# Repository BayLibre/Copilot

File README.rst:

Copilot
=======

.. image:: doc/source/pictures/copilot_lite_top.jpg

Description
-----------

The user documentation is available in the ``doc`` folder.
The generated HTML pages can be viewed `here <https://baylibre.github.io/Copilot/>`_.

The board hardware files are in the ``Copilot_Lite/Hardware`` folder.

The FTDI chip is configured and serialized by the ``Serialization`` software located in the  ``Copilot_Lite/Software`` folder.
The boards serialization and test procedure is described in the ``Copilot_Lite/Factory_Testing.md`` file.

Extension boards
----------------

The Copilot Lite board features some extension boards to be connected on top, like an Arduino Shield or a Raspberry Pi Hat.

More than one extension board can be stacked on top of the Copilot Lite master board, according to the needs.

* `3x USB 2.0 channels <https://github.com/BayLibre/Copilot-extension-triple-usb-2.0>`_, the Copilot Lite GPIOs can drive the channels power.
* `3x signal relays <https://github.com/BayLibre/Copilot_Extension_Triple_Relays>`_, the Copilot Lite GPIOs can close or open each relay.

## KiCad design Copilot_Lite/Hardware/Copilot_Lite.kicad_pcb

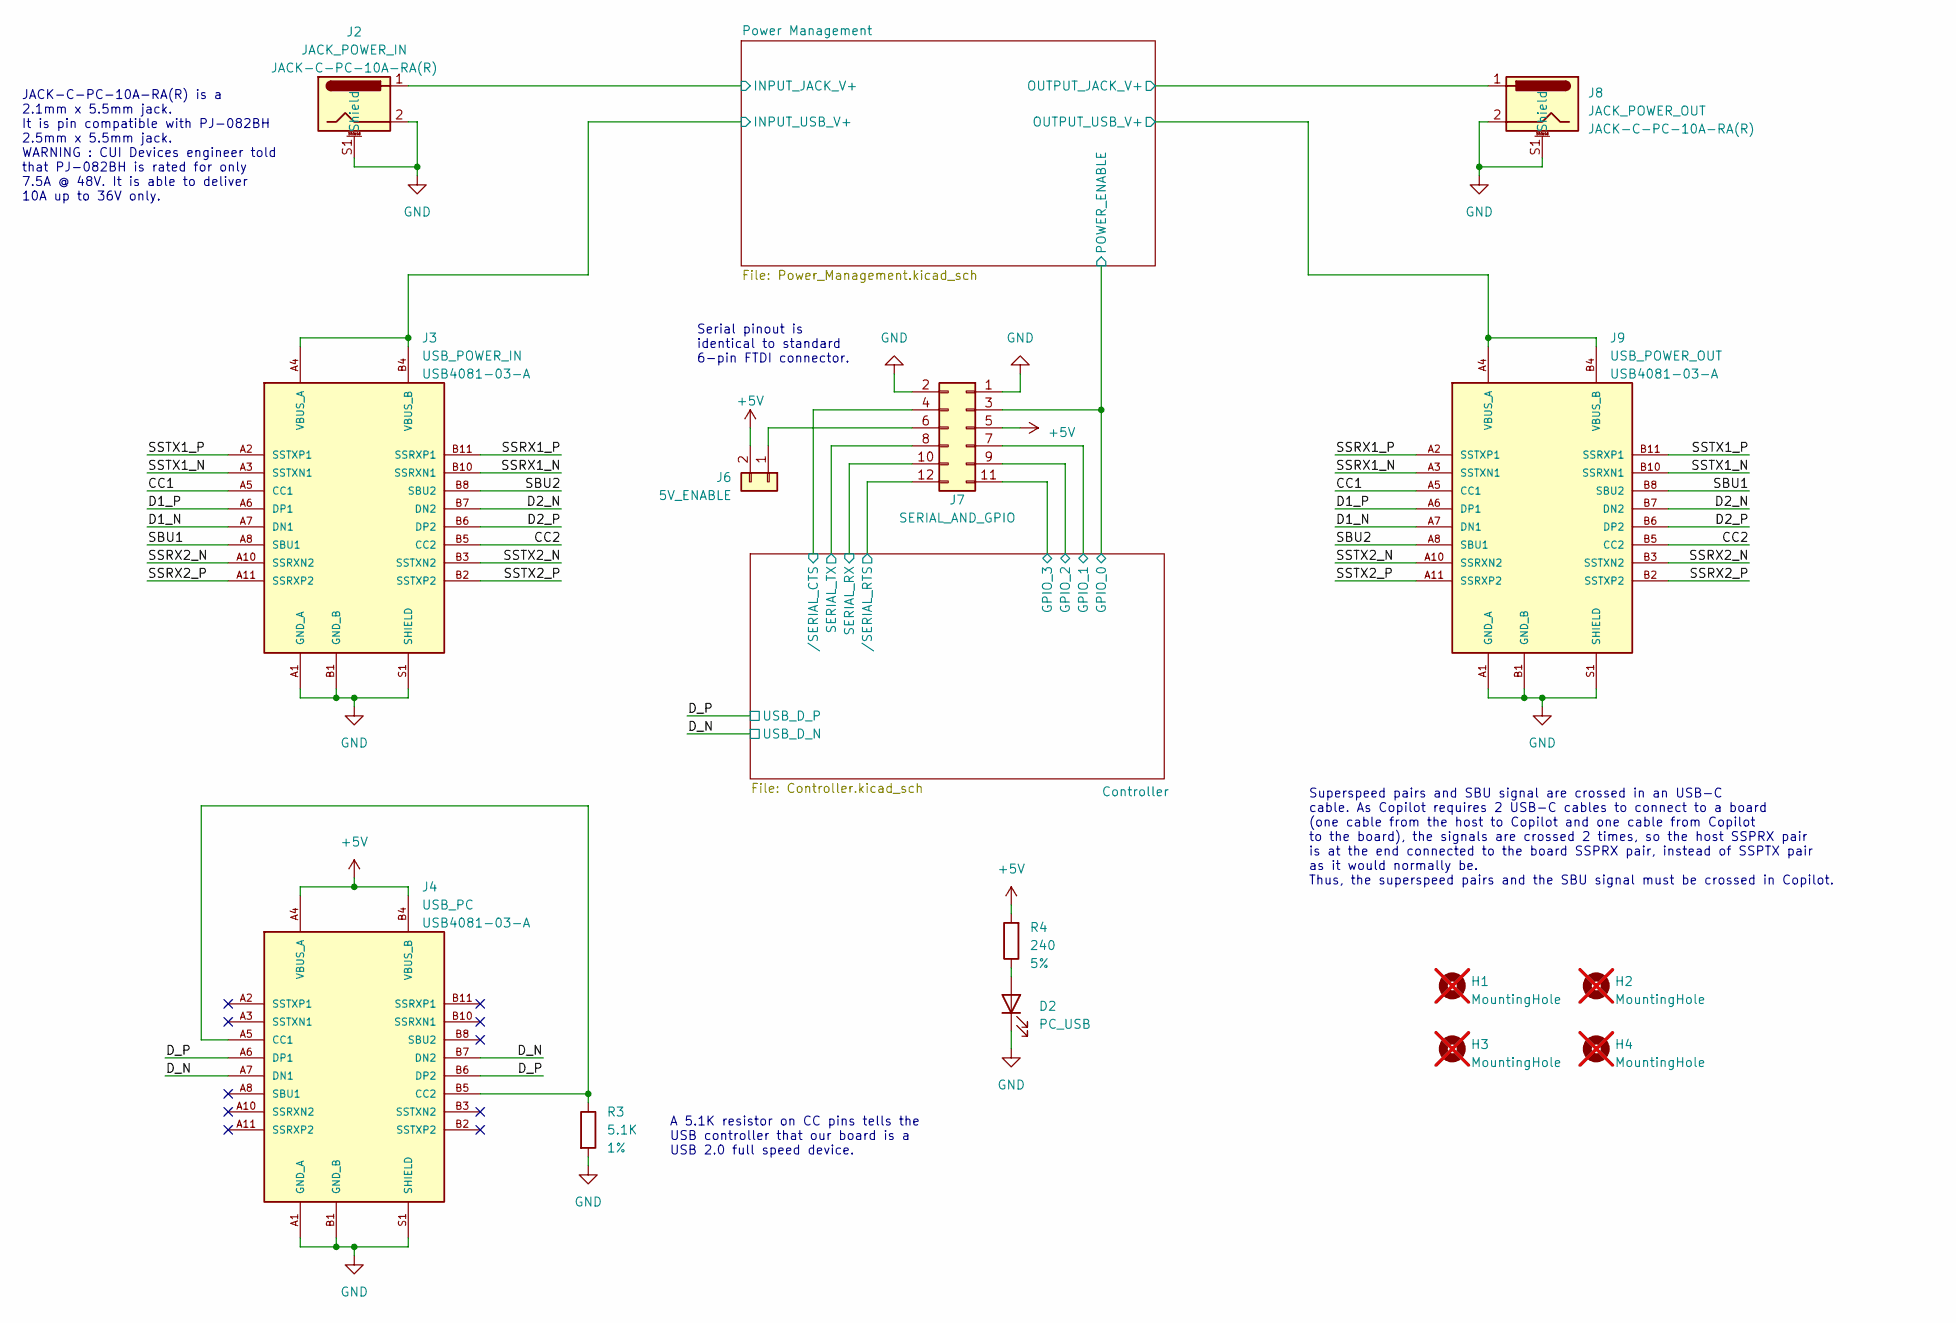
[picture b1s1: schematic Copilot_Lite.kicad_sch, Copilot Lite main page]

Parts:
D2: PC_USB; LED_0805_2012Metric; PartNumber 150080SS75000
H1, H2, H3, H4: MountingHole; MountingHole_2.7mm; not fitted
J2: JACK_POWER_IN; JACK-C-PC-10A-RA(R); PartNumber JACK-C-PC-10A-RA(R)
J3: USB_POWER_IN; USB4081-03-A; PartNumber USB4081-03-A
J4: USB_PC; USB4081-03-A; PartNumber USB4081-03-A
J6: 5V_ENABLE; PinHeader_1x02_P2.54mm_Horizontal
J7: SERIAL_AND_GPIO; PinHeader_2x06_P2.54mm_Horizontal
J8: JACK_POWER_OUT; JACK-C-PC-10A-RA(R); PartNumber JACK-C-PC-10A-RA(R)
J9: USB_POWER_OUT; USB4081-03-A; PartNumber USB4081-03-A
R3: 5.1K; R_0603_1608Metric; PartNumber RC0603FR-075K1L
R4: 240; R_1206_3216Metric; PartNumber RC1206JR-07240RL

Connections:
+5V: J4.A4 (VBUS_A), J4.A9 (VBUS_A), J4.B4 (VBUS_B), J4.B9 (VBUS_B), J6.2, J7.5, R4.2; also elsewhere on the board
/CC1: J3.A5 (CC1), J9.A5 (CC1)
/CC2: J3.B5 (CC2), J9.B5 (CC2)
/Controller/GPIO_0: J7.3; also elsewhere on the board
/Controller/GPIO_1: J7.7; also elsewhere on the board
/Controller/GPIO_2: J7.9; also elsewhere on the board
/Controller/GPIO_3: J7.11; also elsewhere on the board
/Controller/SERIAL_RX: J7.10; also elsewhere on the board
/Controller/SERIAL_TX: J7.8; also elsewhere on the board
/Controller//SERIAL_CTS: J7.4; also elsewhere on the board
/Controller//SERIAL_RTS: J7.12; also elsewhere on the board
/D1_N: J3.A7 (DN1), J9.A7 (DN1)
/D1_P: J3.A6 (DP1), J9.A6 (DP1)
/D2_N: J3.B7 (DN2), J9.B7 (DN2)
/D2_P: J3.B6 (DP2), J9.B6 (DP2)
/D_N: J4.A7 (DN1), J4.B7 (DN2); also elsewhere on the board
/D_P: J4.A6 (DP1), J4.B6 (DP2); also elsewhere on the board
/Power Management/INPUT_JACK_V+: J2.1; also elsewhere on the board
/Power Management/INPUT_USB_V+: J3.A4 (VBUS_A), J3.A9 (VBUS_A), J3.B4 (VBUS_B), J3.B9 (VBUS_B); also elsewhere on the board
/Power Management/OUTPUT_JACK_V+: J8.1; also elsewhere on the board
/Power Management/OUTPUT_USB_V+: J9.A4 (VBUS_A), J9.A9 (VBUS_A), J9.B4 (VBUS_B), J9.B9 (VBUS_B); also elsewhere on the board
/SBU1: J3.A8 (SBU1), J9.B8 (SBU2)
/SBU2: J3.B8 (SBU2), J9.A8 (SBU1)
/SSRX1_N: J3.B10 (SSRXN1), J9.A3 (SSTXN1)
/SSRX1_P: J3.B11 (SSRXP1), J9.A2 (SSTXP1)
/SSRX2_N: J3.A10 (SSRXN2), J9.B3 (SSTXN2)
/SSRX2_P: J3.A11 (SSRXP2), J9.B2 (SSTXP2)
/SSTX1_N: J3.A3 (SSTXN1), J9.B10 (SSRXN1)
/SSTX1_P: J3.A2 (SSTXP1), J9.B11 (SSRXP1)
/SSTX2_N: J3.B3 (SSTXN2), J9.A10 (SSRXN2)
/SSTX2_P: J3.B2 (SSTXP2), J9.A11 (SSRXP2)
GND: D2.1 (K), J2.2, J2.S1 (Shield), J2.S2 (Shield), J2.S3 (Shield), J2.S4 (Shield), J3.A1 (GND_A), J3.A12 (GND_A), J3.B1 (GND_B), J3.B12 (GND_B), J3.S1 (SHIELD), J3.S2 (SHIELD), J3.S3 (SHIELD), J3.S4 (SHIELD), J3.S5 (SHIELD), J3.S6 (SHIELD), J4.A1 (GND_A), J4.A12 (GND_A), J4.B1 (GND_B), J4.B12 (GND_B), J4.S1 (SHIELD), J4.S2 (SHIELD), J4.S3 (SHIELD), J4.S4 (SHIELD), J4.S5 (SHIELD), J4.S6 (SHIELD), J7.1, J7.2, J8.2, J8.S1 (Shield), J8.S2 (Shield), J8.S3 (Shield), J8.S4 (Shield), J9.A1 (GND_A), J9.A12 (GND_A), J9.B1 (GND_B), J9.B12 (GND_B), J9.S1 (SHIELD), J9.S2 (SHIELD), J9.S3 (SHIELD), J9.S4 (SHIELD), J9.S5 (SHIELD), J9.S6 (SHIELD), R3.2; also elsewhere on the board
unnamed: D2.2 (A), R4.1
unnamed: J4.A5 (CC1), J4.B5 (CC2), R3.1
unnamed: J6.1, J7.6

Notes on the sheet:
A 5.1K resistor on CC pins tells the USB controller that our board is a USB 2.0 full speed device.
JACK-C-PC-10A-RA(R) is a 2.1mm x 5.5mm jack. It is pin compatible with PJ-082BH 2.5mm x 5.5mm jack. WARNING : CUI Devices engineer told that PJ-082BH is rated for only 7.5A @ 48V. It is able to deliver 10A up to 36V only.
Superspeed pairs and SBU signal are crossed in an USB-C cable. As Copilot requires 2 USB-C cables to connect to a board (one cable from the host to Copilot and one cable from Copilot to the board), the signals are crossed 2 times, so the host SSPRX pair is at the end connected to the board SSPRX pa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
Serial pinout is identical to standard 6-pin FTDI connector.

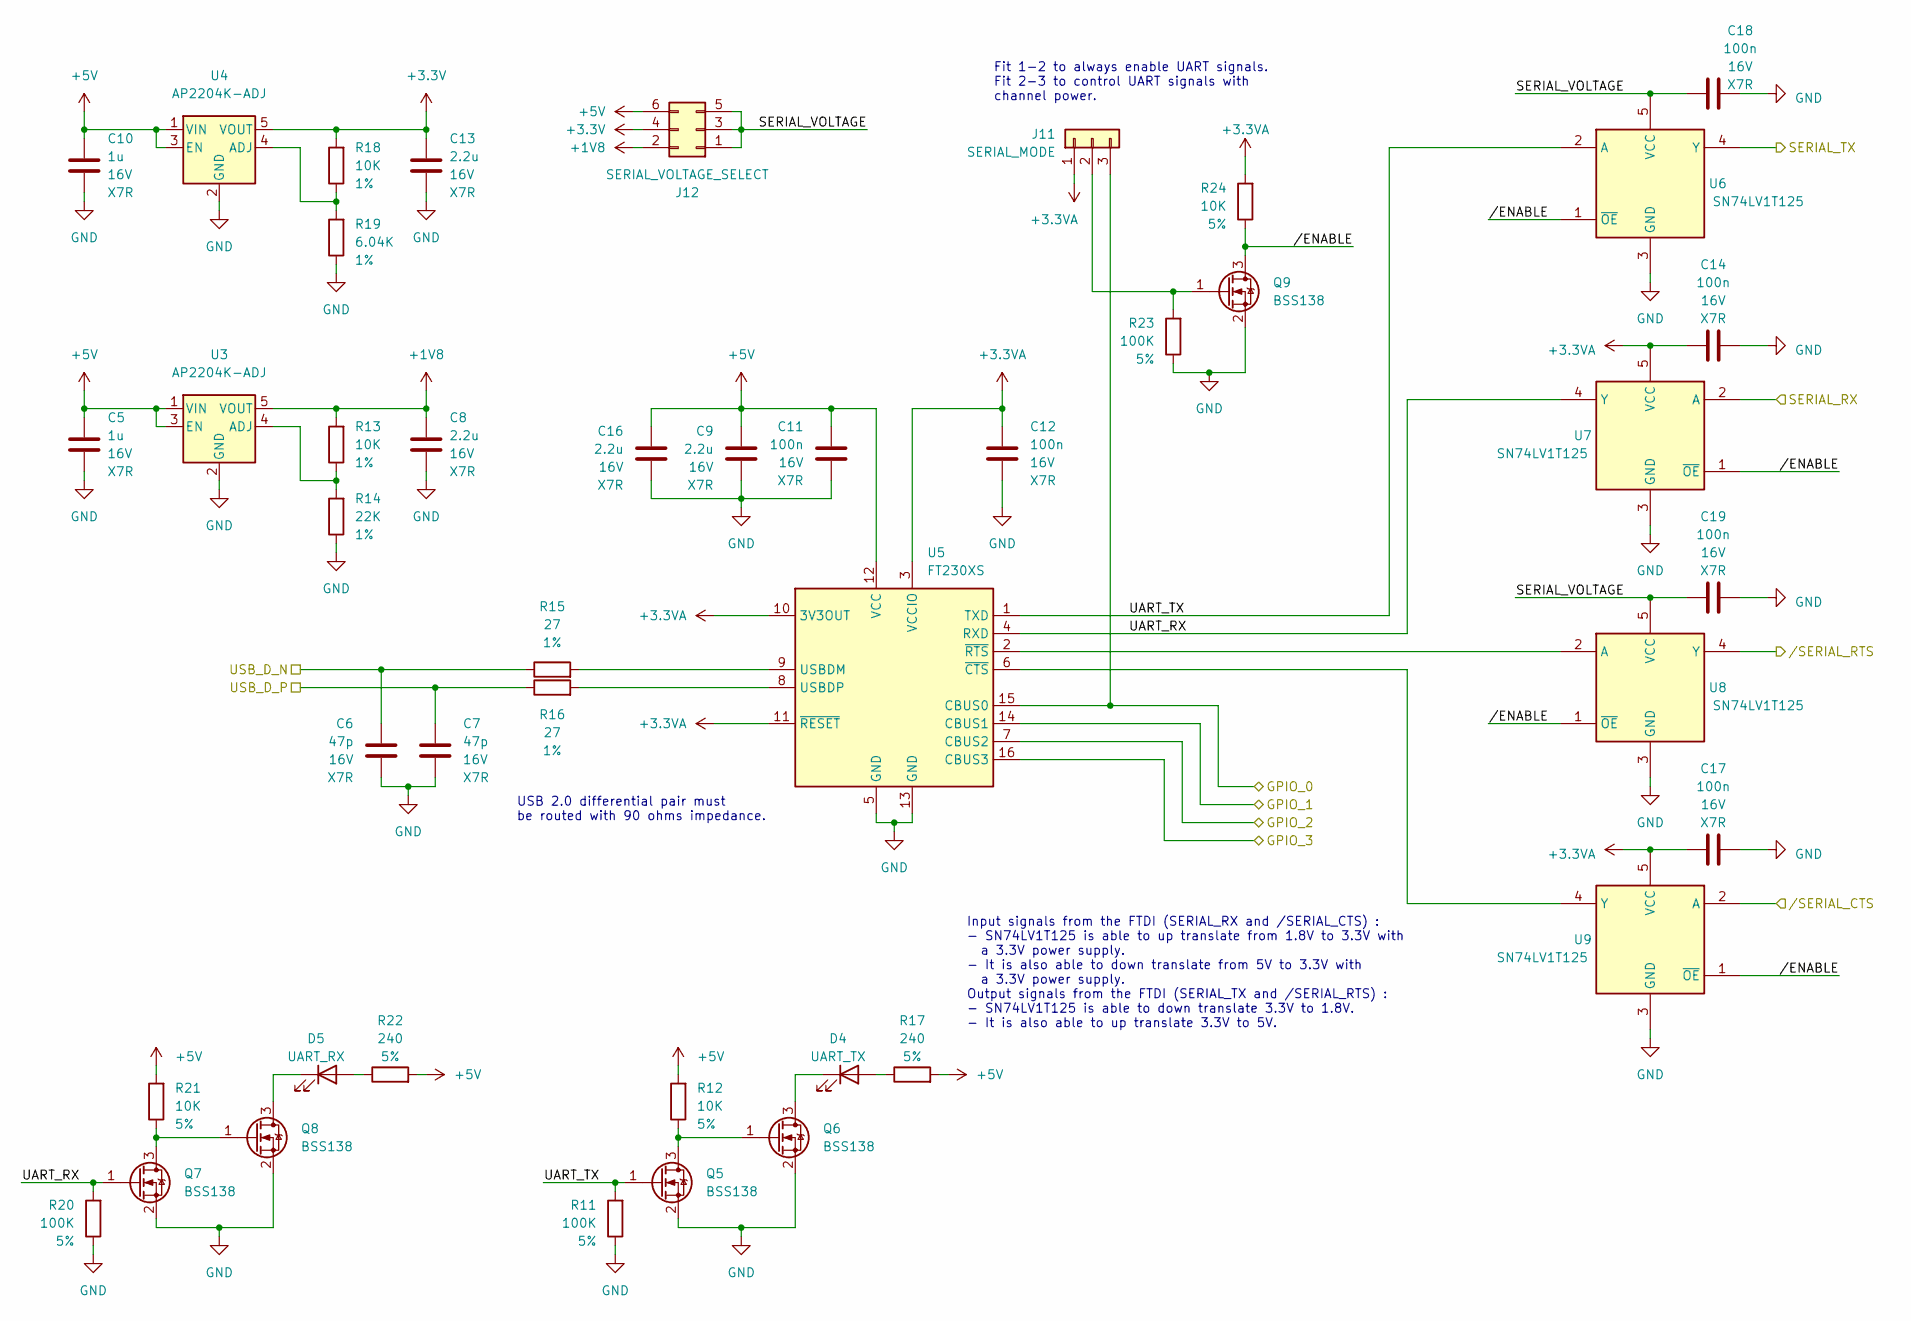
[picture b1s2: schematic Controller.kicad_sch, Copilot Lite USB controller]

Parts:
C5, C10: 1u; C_0603_1608Metric; PartNumber CL10A105KO8NNNC
C6, C7: 47p; C_0603_1608Metric; PartNumber CL10C470JB81PNC
C8, C9, C13, C16: 2.2u; C_0603_1608Metric; PartNumber CL10A225KO8NNNC
C11, C12, C14, C17, C18, C19: 100n; C_0603_1608Metric; PartNumber CL10B104KO8NNNC
D4: UART_TX; LED_0805_2012Metric; PartNumber 150080SS75000
D5: UART_RX; LED_0805_2012Metric; PartNumber 150080SS75000
J11: SERIAL_MODE; PinHeader_1x03_P2.54mm_Horizontal
J12: SERIAL_VOLTAGE_SELECT; PinHeader_2x03_P2.54mm_Horizontal
Q5, Q6, Q7, Q8, Q9: BSS138; SOT-23; PartNumber BSS138P,215
R11, R20, R23: 100K; R_0603_1608Metric; PartNumber RC0603FR-07100KL
R12, R13, R18, R21, R24: 10K; R_0603_1608Metric; PartNumber RNCP0603FTD10K0
R14: 22K; R_0603_1608Metric; PartNumber RC0603FR-0722KL
R15, R16: 27; R_0603_1608Metric; PartNumber RC0603FR-1327RL
R17, R22: 240; R_1206_3216Metric; PartNumber RC1206JR-07240RL
R19: 6.04K; R_0603_1608Metric; PartNumber RC0603FR-076K04L
U3, U4: AP2204K-ADJ; SOT-23-5; PartNumber AP2204K-ADJTRG1
U5: FT230XS; SSOP-16_3.9x4.9mm_P0.635mm; PartNumber FT230XS-R
U6, U7, U8, U9: SN74LV1T125; SOT-23-5; PartNumber SN74LV1T125DBV

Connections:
+1V8: C8.1, J12.2, R13.2, U3.5 (VOUT)
+3.3V: C13.1, J12.4, R18.2, U4.5 (VOUT)
+3.3VA: C12.1, C14.1, C17.1, J11.1, R24.2, U5.3 (VCCIO), U5.10 (3V3OUT), U5.11 (~RESET), U7.5 (VCC), U9.5 (VCC)
+5V: C5.1, C9.1, C10.1, C11.1, C16.1, J12.6, R12.2, R17.2, R21.2, R22.2, U3.1 (VIN), U3.3 (EN), U4.1 (VIN), U4.3 (EN), U5.12 (VCC); also elsewhere on the board
/Controller/GPIO_0: J11.3, U5.15 (CBUS0); also elsewhere on the board
/Controller/GPIO_1: U5.14 (CBUS1); also elsewhere on the board
/Controller/GPIO_2: U5.7 (CBUS2); also elsewhere on the board
/Controller/GPIO_3: U5.16 (CBUS3); also elsewhere on the board
/Controller/SERIAL_RX: U7.2 (A); also elsewhere on the board
/Controller/SERIAL_TX: U6.4 (Y); also elsewhere on the board
/Controller/SERIAL_VOLTAGE: C18.1, C19.1, J12.1, J12.3, J12.5, U6.5 (VCC), U8.5 (VCC)
/Controller/UART_RX: Q7.1 (G), R20.2, U5.4 (RXD), U7.4 (Y)
/Controller/UART_TX: Q5.1 (G), R11.2, U5.1 (TXD), U6.2 (A)
/Controller//ENABLE: Q9.3 (D), R24.1, U6.1 (~OE), U7.1 (~OE), U8.1 (~OE), U9.1 (~OE)
/Controller//SERIAL_CTS: U9.2 (A); also elsewhere on the board
/Controller//SERIAL_RTS: U8.4 (Y); also elsewhere on the board
/D_N: C6.1, R15.1; also elsewhere on the board
/D_P: C7.1, R16.1; also elsewhere on the board
GND: C5.2, C6.2, C7.2, C8.2, C9.2, C10.2, C11.2, C12.2, C13.2, C14.2, C16.2, C17.2, C18.2, C19.2, Q5.2 (S), Q6.2 (S), Q7.2 (S), Q8.2 (S), Q9.2 (S), R11.1, R14.1, R19.1, R20.1, R23.1, U3.2 (GND), U4.2 (GND), U5.5 (GND), U5.13 (GND), U6.3 (GND), U7.3 (GND), U8.3 (GND), U9.3 (GND); also elsewhere on the board
unnamed: D4.2 (A), R17.1
unnamed: D4.1 (K), Q6.3 (D)
unnamed: D5.2 (A), R22.1
unnamed: D5.1 (K), Q8.3 (D)
unnamed: J11.2, Q9.1 (G), R23.2
unnamed: Q5.3 (D), Q6.1 (G), R12.1
unnamed: Q7.3 (D), Q8.1 (G), R21.1
unnamed: R13.1, R14.2, U3.4 (ADJ)
unnamed: R18.1, R19.2, U4.4 (ADJ)
unnamed: R15.2, U5.9 (USBDM)
unnamed: R16.2, U5.8 (USBDP)
unnamed: U5.6 (~CTS), U9.4 (Y)
unnamed: U5.2 (~RTS), U8.2 (A)

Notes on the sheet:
Input signals from the FTDI (SERIAL_RX and /SERIAL_CTS) : - SN74LV1T125 is able to up translate from 1.8V to 3.3V with a 3.3V power supply. - It is also able to down translate from 5V to 3.3V with a 3.3V power supply. Output signals from the FTDI (SERIAL_TX and /SERIAL_RTS) : - SN74LV1T125 is able 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
USB 2.0 differential pair must be routed with 90 ohms impedance.
Fit 1-2 to always enable UART signals. Fit 2-3 to control UART signals with channel power.

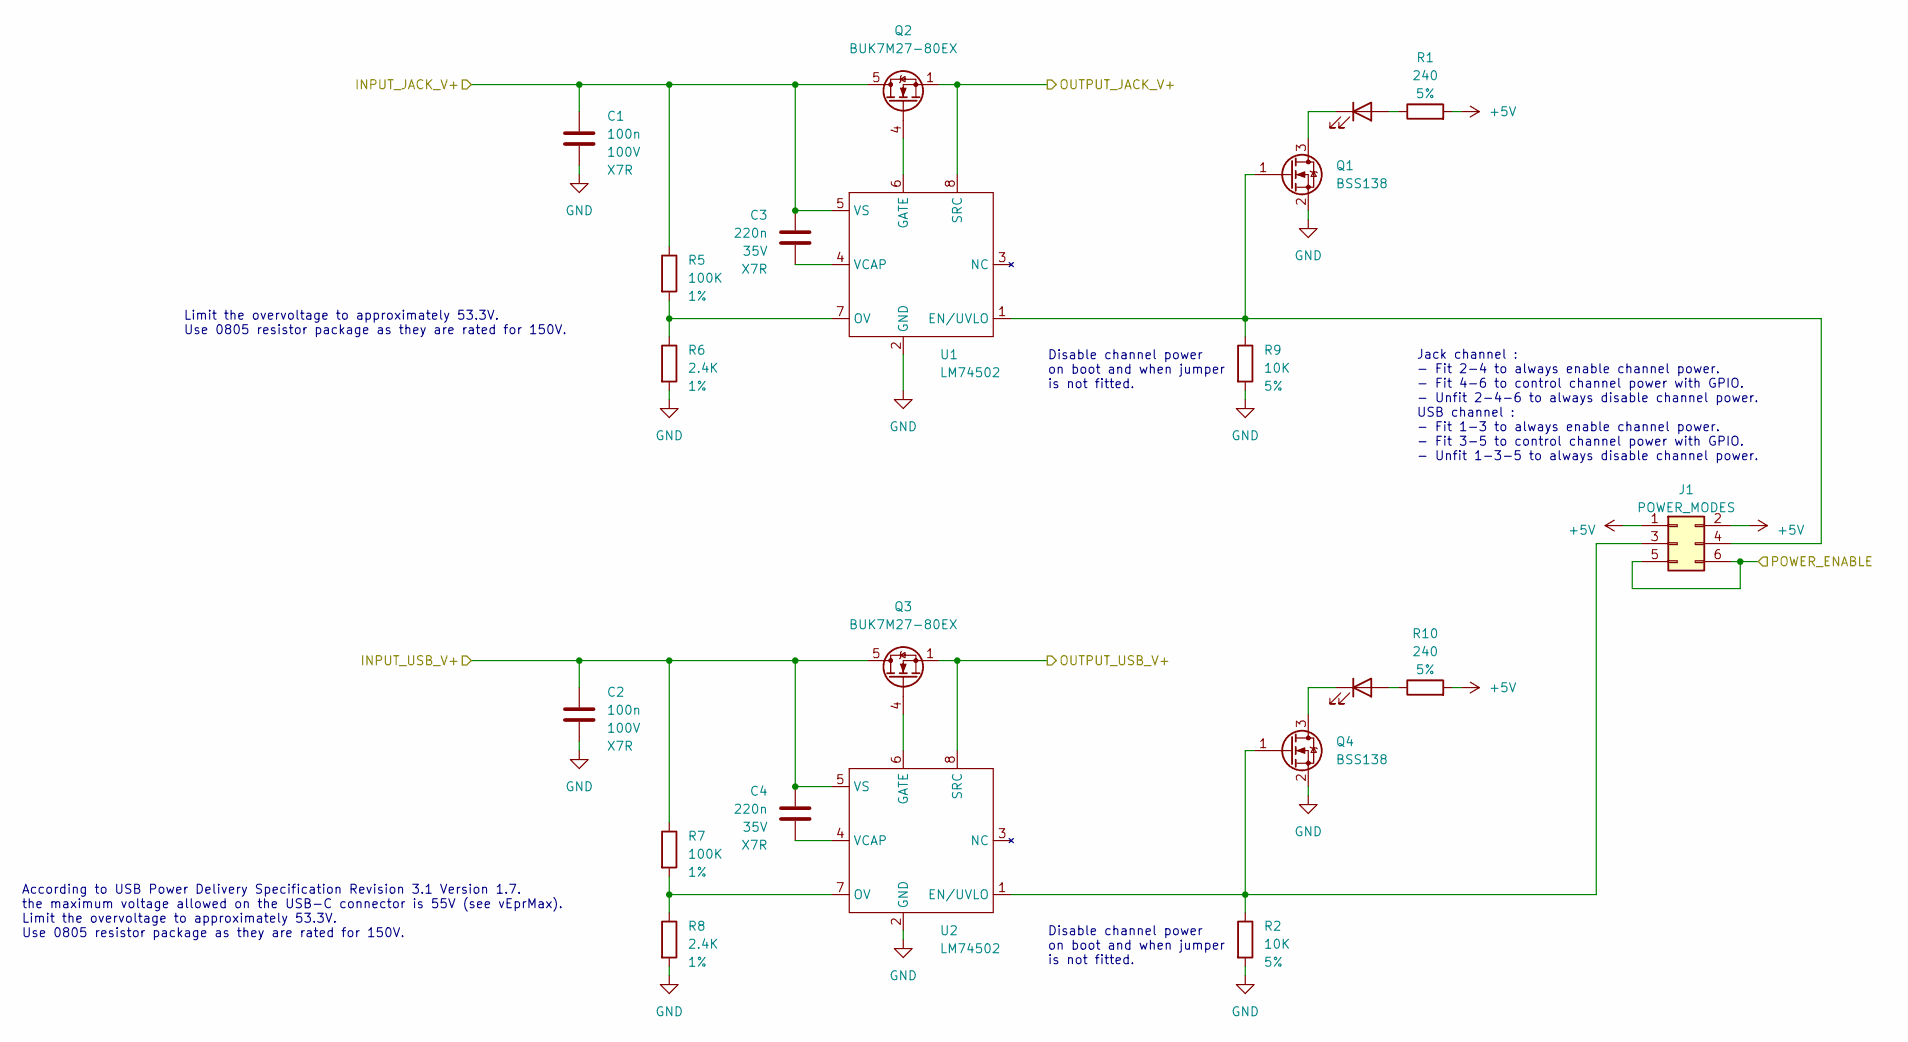
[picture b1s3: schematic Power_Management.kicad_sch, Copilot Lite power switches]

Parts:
C1, C2: 100n; C_0805_2012Metric; PartNumber CL21B104KCFNNNE
C3, C4: 220n; C_0805_2012Metric; PartNumber CL21B224KBFNNNE
D1, D3: POWER_SWITCH; LED_0805_2012Metric; PartNumber 150080SS75000
J1: POWER_MODES; PinHeader_2x03_P2.54mm_Horizontal
Q1, Q4: BSS138; SOT-23; PartNumber BSS138P,215
Q2, Q3: BUK7M27-80EX; LFPAK33; PartNumber BUK7M27-80EX
R1, R10: 240; R_1206_3216Metric; PartNumber RC1206JR-07240RL
R2, R9: 10K; R_0603_1608Metric; PartNumber RNCP0603FTD10K0
R5, R7: 100K; R_0805_2012Metric; PartNumber RMCF0805FT100K
R6, R8: 2.4K; R_0805_2012Metric; PartNumber RC0805FR-072K4L
U1, U2: LM74502; SOT-23-8; PartNumber LM74502DDFR

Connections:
+5V: J1.1, J1.2, R1.2, R10.2; also elsewhere on the board
/Controller/GPIO_0: J1.5, J1.6; also elsewhere on the board
/Power Management/INPUT_JACK_V+: C1.1, C3.1, Q2.5 (D), R5.1, U1.5 (VS); also elsewhere on the board
/Power Management/INPUT_USB_V+: C2.1, C4.1, Q3.5 (D), R7.1, U2.5 (VS); also elsewhere on the board
/Power Management/OUTPUT_JACK_V+: Q2.1 (S), Q2.2 (S), Q2.3 (S), U1.8 (SRC); also elsewhere on the board
/Power Management/OUTPUT_USB_V+: Q3.1 (S), Q3.2 (S), Q3.3 (S), U2.8 (SRC); also elsewhere on the board
GND: C1.2, C2.2, Q1.2 (S), Q4.2 (S), R2.2, R6.2, R8.2, R9.2, U1.2 (GND), U2.2 (GND); also elsewhere on the board
unnamed: D1.2 (A), R1.1
unnamed: D1.1 (K), Q1.3 (D)
unnamed: D3.2 (A), R10.1
unnamed: D3.1 (K), Q4.3 (D)
unnamed: J1.3, Q4.1 (G), R2.1, U2.1 (EN/UVLO)
unnamed: J1.4, Q1.1 (G), R9.1, U1.1 (EN/UVLO)
unnamed: Q2.4 (G), U1.6 (GATE)
unnamed: Q3.4 (G), U2.6 (GATE)
unnamed: R5.2, R6.1, U1.7 (OV)
unnamed: C3.2, U1.4 (VCAP)
unnamed: R7.2, R8.1, U2.7 (OV)
unnamed: C4.2, U2.4 (VCAP)

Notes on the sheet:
According to USB Power Delivery Specification Revision 3.1 Version 1.7. the maximum voltage allowed on the USB-C connector is 55V (see vEprMax). Limit the overvoltage to approximately 53.3V. Use 0805 resistor package as they are rated for 150V.
Disable channel power on boot and when jumper is not fitted.
Jack channel : - Fit 2-4 to always enable channel power. - Fit 4-6 to control channel power with GPIO. - Unfit 2-4-6 to always disable channel power. USB channel : - Fit 1-3 to always enable channel power. - Fit 3-5 to control channel power with GPIO. - Unfit 1-3-5 to always disable channel power.
Limit the overvoltage to approximately 53.3V. Use 0805 resistor package as they are rated for 150V.

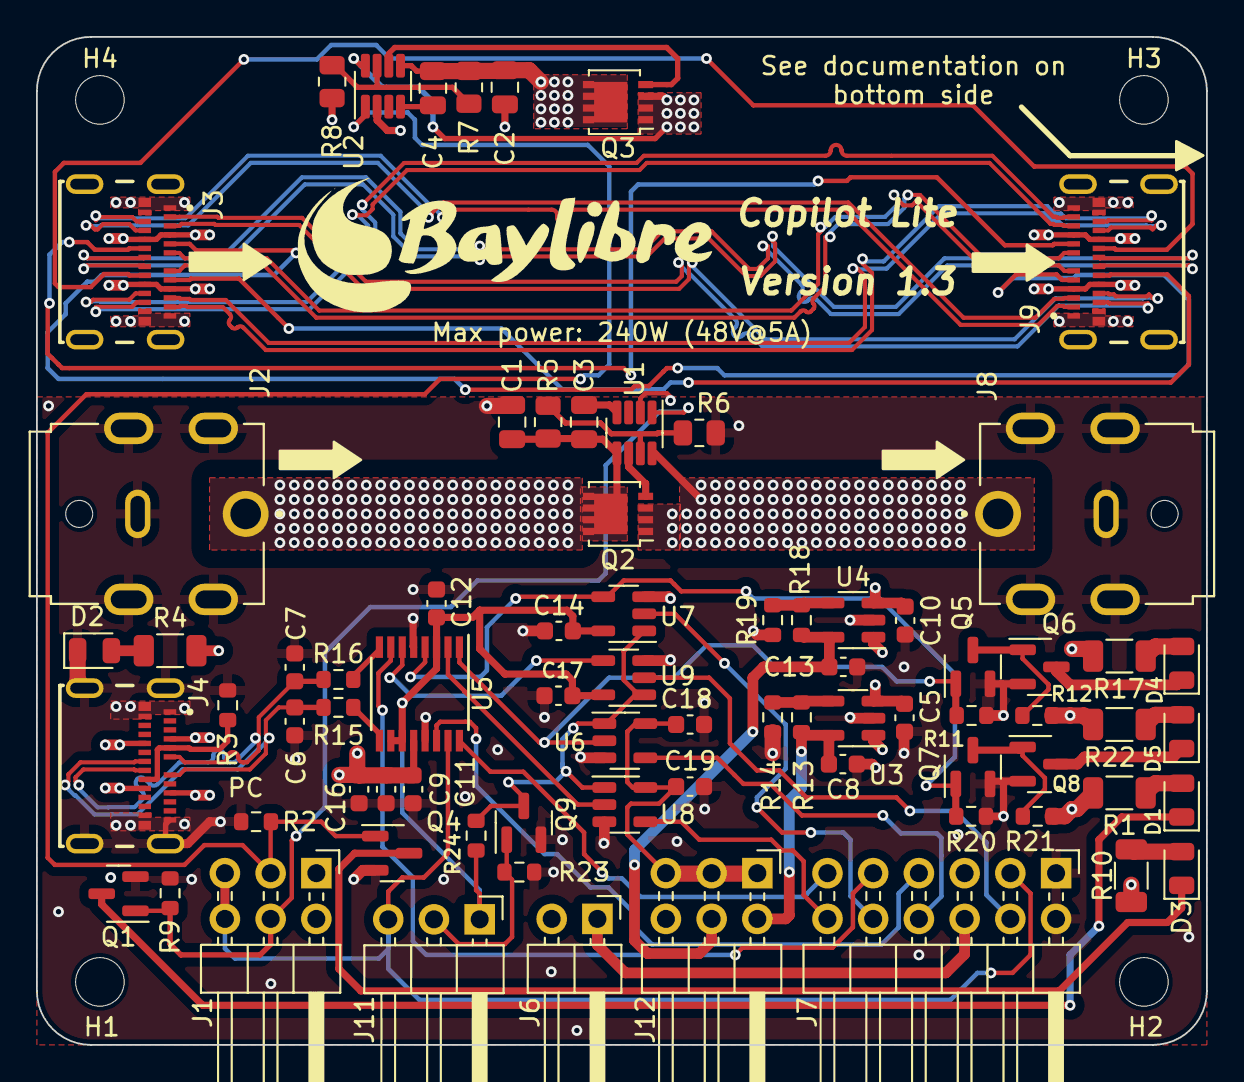
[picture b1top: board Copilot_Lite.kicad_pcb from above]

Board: 4 copper layers, 65.0 x 56.0 mm, 79 parts (0 on the bottom side), 67 nets.

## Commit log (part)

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2023-08-25 Initial commit. Added empty uCIme Lite KiCAD project.
2023-08-25 lite: Added LM74502 symbol, used KiCAD-provided SOT-23-8 footprint and 3D model.
2023-08-25 lite: Added 2.1mm JACK-C-PC-10A-RA(R) power jack symbol, footprint and 3D model in addition with pin-compatible 2.5mm PJ-082BH jack.
2023-08-25 lite: Added power jack power control schematic.
2023-08-25 lite: Added USB4081 USB-C connector symbol, footprint and 3D model.
2023-08-25 lite: Added USB-C connectors power control and data passthrough.
2023-08-25 lite: Added FTDI USB connector, power supplies and USB differential pair to schematic.
2023-08-25 lite: Added serial and USB connectors. A voltage translator is provided on the serial ports for the user to select the appropriate board voltage. No voltage translator is provided on the FTDI GPIO pi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
2023-08-25 lite: Added the LDOs for the serial port voltage translator.
2023-08-25 lite: Added jumpers to control the power channel mode (always enabled, always disabled or controlled by a FTDI GPIO).
2023-08-25 lite: Added leds to schematic. One led for power switch, and two for UART TX and RX.
2023-08-25 lite: Added a led that lights when PC USB connector is plugged.
2023-08-25 lite: Switched project to KiCad 7.
2023-08-25 lite: Added a dedicated mode selection jumper per power channel. This allows to fit custom requirements, like disabling the USB power while keeping the USB connected and driving the board power with 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
2023-08-25 lite: Named components in the schematic and added some part numbers.
2023-08-25 lite: Updated the schematic symbols that have changed in KiCad 7.
2023-08-25 lite: Added more part numbers to the schematic. Replaced the FTDI 4.7u capacitor by two 2.2u capacitors to improve the BoM.
2023-08-25 lite: Added to schematic all missing part numbers but the pin header ones.
2023-08-25 lite: Displayed the all capacitor and resistor relevant parameters on the schematic.
2023-08-25 lite: Configured PCB stackup and placed connectors.
2023-08-25 lite: Replaced power input pins from USB-C connector by passive pins to avoid the USB-C powers being shorted in the schematic.
2023-08-25 lite: Routed power USB-C High Speed and Super Speed differential pairs (without trace length matching for now).
2023-08-25 lite: Finished routing all power USB-C connectors signals.
2023-08-25 lite: Routed power jack high-power traces.
2023-08-25 lite: Routed FTDI USB-C connector.
2023-08-25 lite: Matched quite all USB connectors differential pair length.
2023-08-25 lite: Updated serial and GPIO double-row pin header connector in PCB.
    Also moved a bit the pin headers out of the PCB to make some room for the remaining components.
2023-08-25 lite: Routed jack power channel gate driver.
2023-08-25 lite: Merged jack and USB power modes single-row pin headers into a double-row pin header to save some space on the PCB, currently only the schematic is updated.
2023-08-25 lite: Updated jack and USB power double-row pin header connector in PCB.
2023-08-25 lite: Routed USB power channel gate driver.
2023-08-25 lite: Placed leds and related transistors onto the PCB.
2023-08-25 lite: Swapped UART RX and UART TX leds in schematic to ease PCB routing.
2023-08-25 lite: Finished routing all remaining signals.
2023-08-25 lite: Placed all PCB component references on silkscreen layer.
2023-08-25 lite: Fixed all PCB warnings.
2023-08-25 lite: Added board usage documentation on PCB silkscreen.
2023-08-25 lite: Added Aisler part number properties in both schematic and PCB.
2023-08-25 lite: Renamed the related files with the final project name.
2023-08-25 lite: Replaced the old 'uCIme' name by the new 'Copilot' one in the board files.
2023-08-25 lite: Replaced 'From power supply' and 'To power supply' PCB texts by arrows, also fixed the maximum channel power PCB text.
2023-08-25 lite: Added BayLibre logo and board name and version to PCB.
2023-08-25 lite: Added SN74LV1T125 voltage translater schematic symbol.
2023-08-25 lite: Replaced the TXB0104 voltage translater by several SN74LV1T125.
    The TXB0104 is not able to translate down to 1.8V on its Vccb supply side if the Vcca supply is 3.3V.
2023-08-25 lite: Cleaned PCB silkscreen and fixed all warnings.
2023-08-25 lite: Added the SN74LV1T125 part numbers to both schematic and PCB.
2023-08-25 lite: Added the schematic and PCB versions.
2023-08-25 lite: Added the component reference to the F.Fab layer of the jack connector footprints.
2023-08-25 lite: Added the component reference to the F.Fab layer of the USB-C connector footprint.
2023-08-25 lite: Updated the jack and USB-C footprints in the PCB to get the component reference text on the F.Fab layer.
2023-08-25 lite: Added a little offset to the USB-C connector shield pins to make sure the connector is well aligned when being soldered.
2023-08-25 lite: Bumped board version to 1.1.
2023-08-25 lite: Swapped UART and GPIO pin header rows in both schematic and PCB.
    This allows to more easily use a mezzanine board.
    It is now possible to solder a single row vertical pin header on the row
    that is located inside the PCB and a right-angled single row pin header on
    the row facing the PCB edge to still get access to the UART pins.
    This way, the GPIOs can reach the mezzanine board and there is no need to
    "forward" the UART signals to the mezzanine board.
2023-08-25 lite: Improved reading of the bottom side documentation text on PCB silkscreen.
2023-08-25 lite: Added a script to panelize the board PCB using the KiKit plugin.
2023-08-25 lite: Increased the trace width between the jack connectors to dissipate more heat.
2023-08-25 lite: Added USB-C connector shell holding pins holes in paste layer.
    This way, solder paste can be directly applied also for the holding pins.
    This will help centering the connector during its soldering in the reflow oven.
2023-08-25 lite: Added a little milling radius to the PCB panel to avoid PCB manufacturer warnings.
2023-08-25 lite: Bumped board version to 1.2.
2023-08-25 lite: Moved the hardware files to a dedicated directory to make room for a 'software' directory.
2023-08-30 lite: serialization: Started FTDI EEPROM serialization program implementation.
    The program is currently capable of detecting a serializable Copilot device.
2023-08-30 lite: serialization: Added FTDI EEPROM reading and string descriptors creation.
2023-08-31 lite: serialization: Finished FTDI EEPROM programming.
    The newer version of the FTDI library now supports the FT230X part, so the
    EEPROM operations could be done with the library API and not by manually
    modifying the memory content.
2023-09-08 lite: hardware: Removed the 1mm milling on the panel as it seems to confuse Aisler.
2023-12-12 ci: add gitlab-ci.yml for building pages
    This build checks on merge requests and publish the html to gitlab
    pages.
2023-12-12 README: add initial readme
2023-12-12 doc: initial commit generated with sphinx-quickstart
2023-12-13 lite: serialization: Increased the Copilot Lite USB product string version to 1.2.
2023-12-13 doc: document udev rules
    These are the very first thing every copilot user would like to set up, in order
    to have a reliable access to the copilot gpiochip.
2023-12-13 doc: getting started: add example helper script
2023-12-13 doc: getting started: add newbie friendly hardware guide
    Add a picture of the board being plugged with some markup.
2023-12-14 doc: getting-started: add link to gitlab repo
    This can be useful for people only have access to the gitlab pages. This way,
    they know where to find the hardware files.
2023-12-15 ci: generate schematics with kicad-cli
    This way, each time the shematic is generated, we have a pdf version available
    for everyone to download.
2023-12-15 doc: getting-started: add link to gitlab artifacts
    Link the generatic schematics on the getting started pages.
2023-12-15 doc: getting-started: fix link to artifacts
    We use 'master' as a branch, not 'main'.
    Fix the link.
    Fixes: 845474b75dda ("doc: getting-started: add link to gitlab artifacts")
    Reported-by: Adrien Ricciardi <aricciardi@baylibre.com>
2024-01-11 doc: index: Add short description
    Short description what copilot is and what it can be used for.
2024-01-11 doc: getting-started: Update power switch documentation
    Rename 'Example commands' to 'Switch power' as these arguments actually
    describe how to switch power on or off. Add some minor updates to the
    helper script.
2024-01-11 doc: getting-started: Add section about UART
2024-01-12 doc: index: fix html rendering
    We need to surround the code-block directive with spaces, otherwise the html
    won't be rendered properly.
    Fix it by adding 2 spaces.
    Fixes: d8dd77967971 ("doc: index: Add short description")
2024-01-12 doc: use .. prompt instead of code-block for commands
    Prompt will automatically add a $ in front of each command, and that $ won't be
    copyable if we copy paste from the html rendering.
    Since it's already widely used in getting-started, use it everywhere.
2024-01-12 doc: getting-started: fix some rendering problems
    Since we use bash $ auto for the copilot.sh commands, we should add $ as well.
    This is needed because we also have comments.
    Surround the tty path with double backquotes (``) which is the syntax used for
    inline verbatim text.
2024-01-12 doc: technical-information: Added this section and added information about the barrel jack power channel.
2024-04-16 doc: tips-and-tricks: convert bullet points to paragraphs
    - Describe challenges with barrel jack connectors
    - Add conversion to 14 AWG
    - Add photo of custom cable
2024-04-25 doc: index: minor grammar clean-up
2024-04-25 doc: getting-started: clean-up and clarify J1 header
    - Unicode characters are fun
    - Make line length consistently <= 80
    - Various small grammar fixes
    - Link to release page
    - Copilot ships with J1 configured with jumpers on 3-5 and 4-6, which
    means USB and the barrel jack are both controlled by the GPIO
2024-04-25 doc: getting-started: add link to interactive BOM
2024-04-25 ci: generate interactive HTML BOM
2024-04-25 doc: technical-information: wrap lines to 80 characters
2025-06-26 doc: getting-started: Improve udev rules
    Skip the symlinks on remove and adapt the filename to the usual naming.
2025-06-27 Improve copilot.sh to honor ID_USB_SERIAL_SHORT already being set
2026-01-12 ci: Port GitLab documentation steps to GitHub Actions.
2026-01-12 ci: Remove the now unused GitLab CI file.
2026-01-12 README: Update the generated documentation link.
2026-01-12 LICENSE: Add MIT license.
2026-01-13 README: Add an intro board picture and more details about the project folders.
2026-01-14 doc: pictures: Add 3D rendering pictures of the Copilot Lite board.
2026-01-18 doc: Fix the broken release links.
2026-01-18 deploy: 5c0108eaecb550ccedf7a6b17836b18c27755701
2026-02-05 Copilot_Lite: Hardware: Update the panelize script to horizontally center the fiducials and add post milling.
2026-02-05 Copilot_Lite: Hardware: Panelize: Restore the panel top side silkscreen text.
2026-02-26 Copilot_Lite: Hardware: Ignore the generated panel files.
2026-03-02 Copilot_Lite: Hardware: Convert the schematic and the PCB to KiCad 9
    Use the most recent files format, so any future board modification can be
    more easily compared with the previous ones.
2026-03-02 Copilot_Lite: Hardware: Increase the PCB copper to edge clearance
    It was missing before due to a misconfiguration.
    This should improve manufacturing reliability.
2026-03-02 Copilot_Lite: Hardware: Bump the board version to 1.3
2026-03-02 Copilot_Lite: Software: Serialization: Bump the board version to 1.3
2026-05-21 Copilot_Lite: Add the factory testing procedure
